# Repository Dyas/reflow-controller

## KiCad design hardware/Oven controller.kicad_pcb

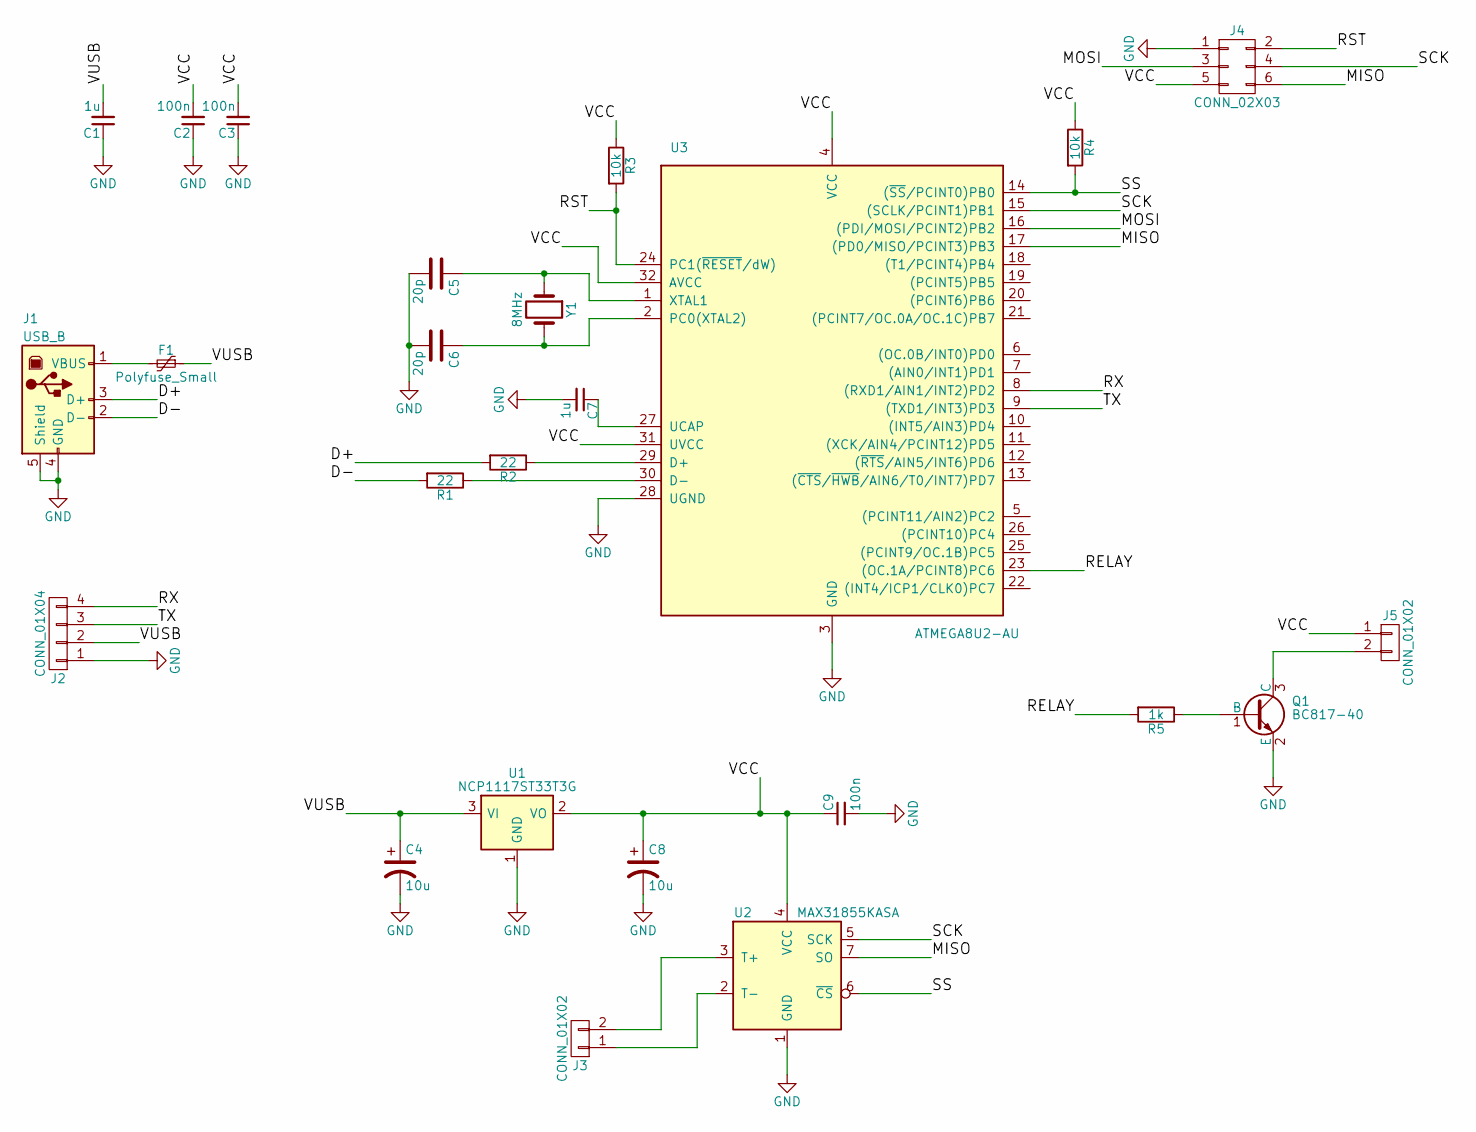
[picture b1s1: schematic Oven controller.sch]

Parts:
C1, C7: 1u; C_1206
C2, C3, C9: 100n; C_1206
C4, C8: 10u; C_1206
C5, C6: 20p; C_0805
F1: Polyfuse_Small; R_1812
J1: USB_B
J2: CONN_01X04; Pin_Header_Angled_1x04_Pitch2.54mm
J3, J5: CONN_01X02; Pin_Header_Angled_1x02_Pitch2.54mm
J4: CONN_02X03; Pin_Header_Angled_2x03_Pitch2.00mm
Q1: BC817-40; SOT-23
R1, R2: 22; R_1206
R3, R4: 10k; R_0805
R5: 1k; R_0805
U1: NCP1117ST33T3G; SOT-223
U2: MAX31855KASA; SOIC-8_3.9x4.9mm_Pitch1.27mm
U3: ATMEGA8U2-AU; TQFP-32_7x7mm_Pitch0.8mm
Y1: 8MHz; Crystal_HC51-U_Vertical

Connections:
/D+: J1.3 (D+), R2.2
/D-: J1.2 (D-), R1.2
/MISO: J4.6, U2.7 (SO), U3.17 ((PD0/MISO/PCINT3)PB3)
/MOSI: J4.3, U3.16 ((PDI/MOSI/PCINT2)PB2)
/RELAY: R5.2, U3.23 ((OC.1A/PCINT8)PC6)
/RST: J4.2, R3.2, U3.24 (PC1(~RESET~/dW))
/RX: J2.4, U3.8 ((RXD1/AIN1/INT2)PD2)
/SCK: J4.4, U2.5 (SCK), U3.15 ((SCLK/PCINT1)PB1)
/SS: R4.2, U2.6 (~CS~), U3.14 ((~SS~/PCINT0)PB0)
/TX: J2.3, U3.9 ((TXD1/INT3)PD3)
/VCC: C2.2, C3.2, C8.1, C9.1, J4.5, J5.1, R3.1, R4.1, U1.2 (VO), U2.4 (VCC), U3.4 (VCC), U3.31 (UVCC), U3.32 (AVCC)
/VUSB: C1.2, C4.1, F1.1, J2.2, U1.3 (VI)
GND: C1.1, C2.1, C3.1, C4.2, C5.2, C6.2, C7.2, C8.2, C9.2, J1.4 (GND), J1.5 (Shield), J2.1, J4.1, Q1.2 (E), U1.1 (GND), U2.1 (GND), U3.3 (GND), U3.28 (UGND)
unnamed: C5.1, U3.1 (XTAL1), Y1.1
unnamed: C6.1, U3.2 (PC0(XTAL2)), Y1.2
unnamed: C7.1, U3.27 (UCAP)
unnamed: F1.2, J1.1 (VBUS)
unnamed: J3.1, U2.2 (T-)
unnamed: J3.2, U2.3 (T+)
unnamed: J5.2, Q1.3 (C)
unnamed: Q1.1 (B), R5.1
unnamed: R1.1, U3.30 (D-)
unnamed: R2.1, U3.29 (D+)

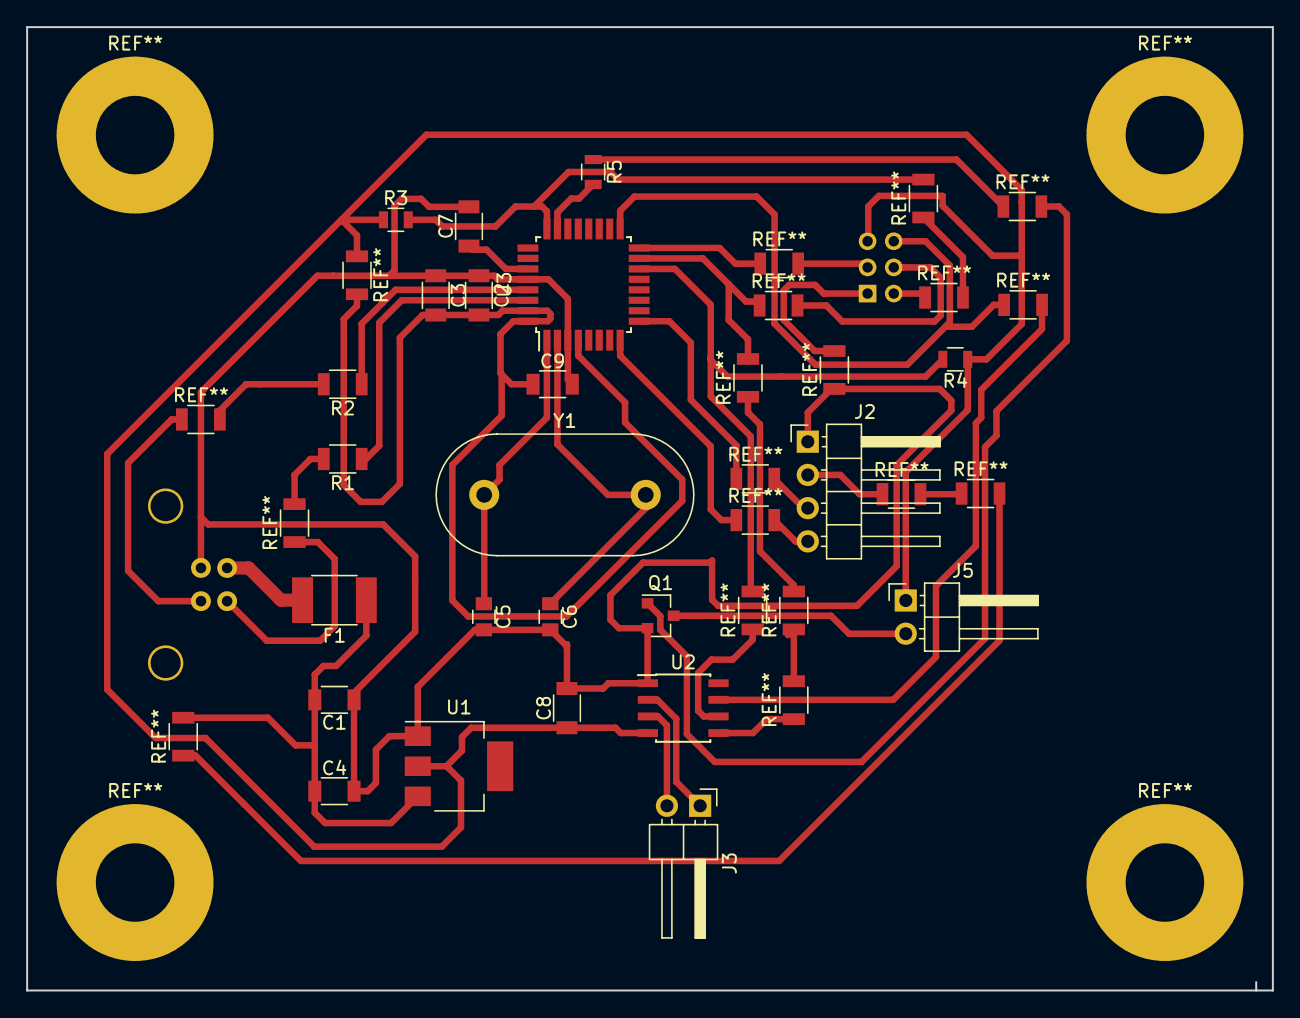
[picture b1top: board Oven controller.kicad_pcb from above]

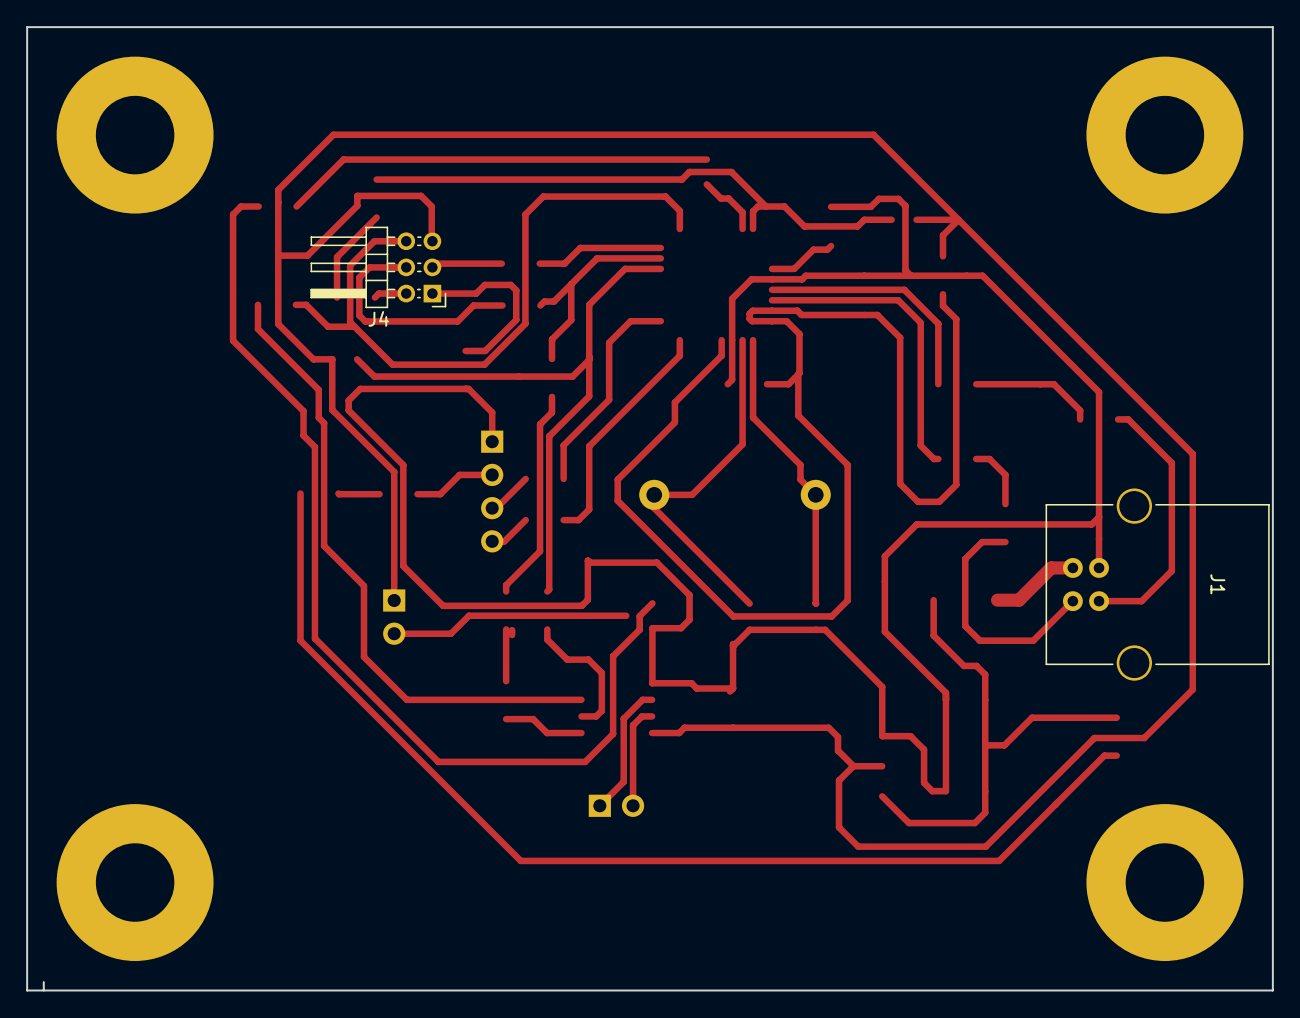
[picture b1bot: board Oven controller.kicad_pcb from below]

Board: 2 copper layers, 95.2 x 73.7 mm, 25 parts (2 on the bottom side), 23 nets.

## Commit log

2017-10-04 Add files via upload
    Henrik's circuit with some changes. I plan to use NCP1117ST33T3G as voltage regulator and USB B connector.
    Made in KiCad.
